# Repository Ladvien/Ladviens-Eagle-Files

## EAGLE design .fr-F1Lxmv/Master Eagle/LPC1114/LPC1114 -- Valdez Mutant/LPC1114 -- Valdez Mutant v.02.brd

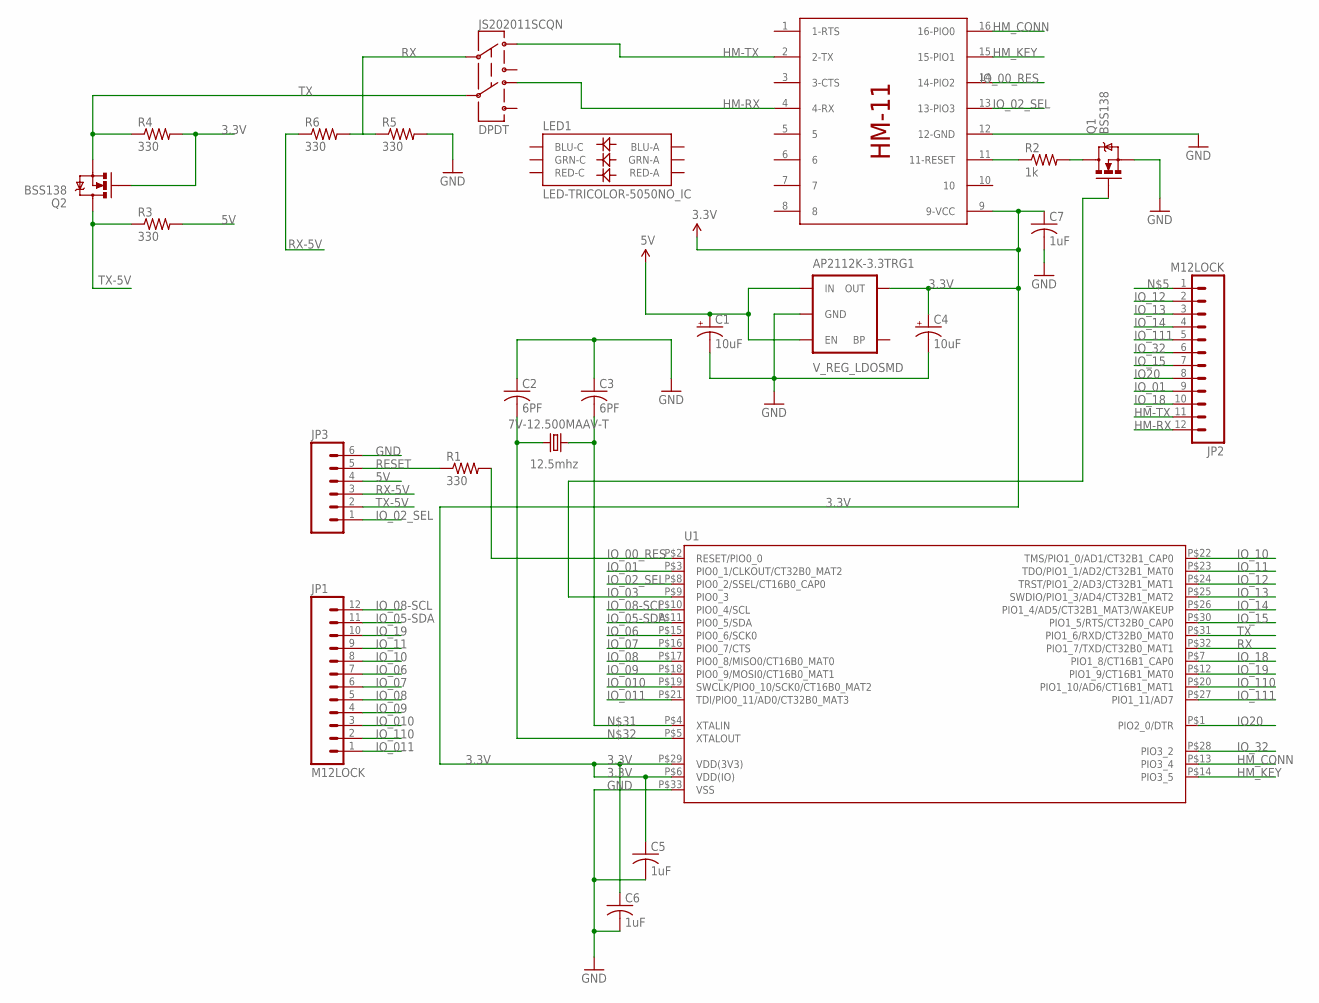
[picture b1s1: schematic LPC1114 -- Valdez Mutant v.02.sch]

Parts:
7V-12.500MAAV-T: 12.5mhz; CRYSTAL-SMD-5X3
AP2112K-3.3TRG1: V_REG_LDOSMD; SOT23-5
C1, C4: 10uF; EIA3216
C2, C3: 6PF; C0402K
C5, C6, C7: 1uF; C0402K
JP1, JP2: M12LOCK; 1X12_LOCK
JP3: M06LOCK; 1X06_LOCK
JS202011SCQN: DPDT; AYZ0202
LED1: LED-TRICOLOR-5050NO_IC; LED-TRICOLOR-5050
Q1, Q2: BSS138; SOT23
R1, R3, R4, R5, R6: 330; R0402
R2: 1k; R0402
U1: LPC1113/4_QFN; HVQFN33-7X7
U$1: HM-11

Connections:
3.3V: AP2112K-3.3TRG1.5 (OUT), C4.A (+), C5.1, C6.1, C7.1, Q2.1 (G), R4.2, U1.P$6 (VDD(IO)), U1.P$29 (VDD(3V3)), U$1.9 (9-VCC)
5V: AP2112K-3.3TRG1.1 (IN), AP2112K-3.3TRG1.3 (EN), C1.A (+), JP3.4, R3.2
GND: AP2112K-3.3TRG1.2 (GND), C1.C (-), C2.1, C3.1, C4.C (-), C5.2, C6.2, C7.2, JP3.6, Q1.2 (S), R5.2, U1.P$33 (VSS), U$1.12 (12-GND)
HM-RX: JP2.12, JS202011SCQN.4, U$1.4 (4-RX)
HM-TX: JP2.11, JS202011SCQN.1, U$1.2 (2-TX)
HM_CONN: U1.P$13 (PIO3_4), U$1.16 (16-PIO0)
HM_KEY: U1.P$14 (PIO3_5), U$1.15 (15-PIO1)
IO20: JP2.8, U1.P$1 (PIO2_0/DTR)
IO_00_RES: R1.2, U1.P$2 (RESET/PIO0_0), U$1.14 (14-PIO2)
IO_01: JP2.9, U1.P$3 (PIO0_1/CLKOUT/CT32B0_MAT2)
IO_02_SEL: JP3.1, U1.P$8 (PIO0_2/SSEL/CT16B0_CAP0), U$1.13 (13-PIO3)
IO_03: Q1.1 (G), U1.P$9 (PIO0_3)
IO_05-SDA: JP1.11, U1.P$11 (PIO0_5/SDA)
IO_06: JP1.7, U1.P$15 (PIO0_6/SCK0)
IO_07: JP1.6, U1.P$16 (PIO0_7/CTS)
IO_08: JP1.5, U1.P$17 (PIO0_8/MISO0/CT16B0_MAT0)
IO_08-SCL: JP1.12, U1.P$10 (PIO0_4/SCL)
IO_09: JP1.4, U1.P$18 (PIO0_9/MOSI0/CT16B0_MAT1)
IO_10: JP1.8, U1.P$22 (TMS/PIO1_0/AD1/CT32B1_CAP0)
IO_010: JP1.3, U1.P$19 (SWCLK/PIO0_10/SCK0/CT16B0_MAT2)
IO_11: JP1.9, U1.P$23 (TDO/PIO1_1/AD2/CT32B1_MAT0)
IO_011: JP1.1, U1.P$21 (TDI/PIO0_11/AD0/CT32B0_MAT3)
IO_12: JP2.2, U1.P$24 (TRST/PIO1_2/AD3/CT32B1_MAT1)
IO_13: JP2.3, U1.P$25 (SWDIO/PIO1_3/AD4/CT32B1_MAT2)
IO_14: JP2.4, U1.P$26 (PIO1_4/AD5/CT32B1_MAT3/WAKEUP)
IO_15: JP2.7, U1.P$30 (PIO1_5/RTS/CT32B0_CAP0)
IO_18: JP2.10, U1.P$7 (PIO1_8/CT16B1_CAP0)
IO_19: JP1.10, U1.P$12 (PIO1_9/CT16B1_MAT0)
IO_32: JP2.6, U1.P$28 (PIO3_2)
IO_110: JP1.2, U1.P$20 (PIO1_10/AD6/CT16B1_MAT1)
IO_111: JP2.5, U1.P$27 (PIO1_11/AD7)
unnamed: Q1.3 (D), R2.2
unnamed: R2.1, U$1.11 (11-RESET)
unnamed: 7V-12.500MAAV-T.3 (2), C3.2, U1.P$4 (XTALIN)
unnamed: 7V-12.500MAAV-T.1, C2.2, U1.P$5 (XTALOUT)
RESET: JP3.5, R1.1
RX: JS202011SCQN.2, R5.1, R6.2, U1.P$32 (PIO1_7/TXD/CT32B0_MAT1)
RX-5V: JP3.3, R6.1
TX: JS202011SCQN.5, Q2.2 (S), R4.1, U1.P$31 (PIO1_6/RXD/CT32B0_MAT0)
TX-5V: JP3.2, Q2.3 (D), R3.1

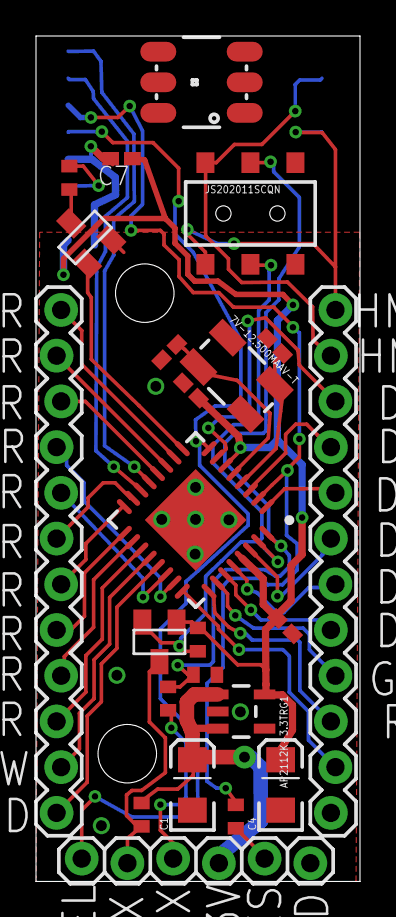
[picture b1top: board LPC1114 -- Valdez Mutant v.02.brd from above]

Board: 2 copper layers, 18.0 x 47.0 mm, 24 parts (1 on the bottom side), 40 nets.

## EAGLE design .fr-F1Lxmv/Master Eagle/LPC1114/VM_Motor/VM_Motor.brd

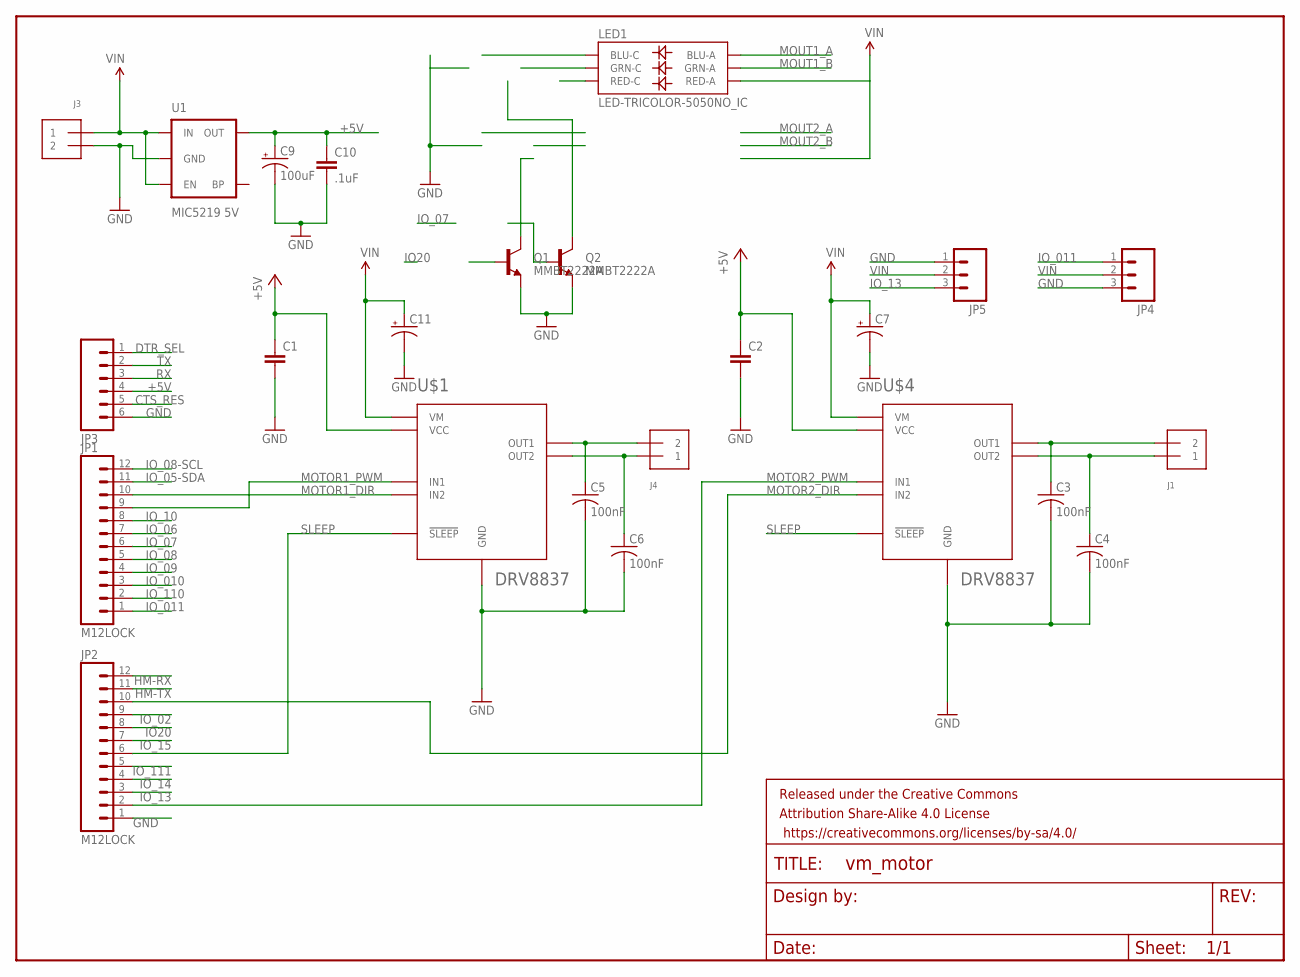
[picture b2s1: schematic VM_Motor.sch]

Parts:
C1, C2: CAP0402-CAP; 0402-CAP
C3, C4, C5, C6: 100nF; C0402
C7, C11: CPOL-US140CLH-0810; 140CLH-0810
C9: 100uF; EIA3528-KIT
C10: .1uF; 0402-CAP
FRAME1: FRAME-LETTER; CREATIVE_COMMONS
J1, J3, J4: TERMBLOCK_1X2; TERMBLOCK_1X2-3.5MM
JP1, JP2: M12LOCK; 1X12_LOCK
JP3: M06LOCK; 1X06_LOCK
JP4, JP5: M03LOCK; 1X03_LOCK
LED1: LED-TRICOLOR-5050NO_IC; LED-TRICOLOR-5050
Q1, Q2: MMBT2222A; SOT23-3
U1: MIC5219 5V; SOT23-5
U$1, U$4: DRV8837; QFN8

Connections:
+5V: C1.1, C2.1, C9.A (+), C10.1, JP3.4, U1.5 (OUT), U$1.P$8 (VCC), U$4.P$8 (VCC)
CTS_RES: JP3.5
DTR_SEL: JP3.1
GND: C1.2, C2.2, C3.2, C4.2, C5.2, C6.2, C7.-, C9.C (-), C10.2, C11.-, J3.2, JP2.1, JP3.6, JP4.3, JP5.1, Q1.2 (E), Q2.2 (E), U1.2 (GND), U$1.P$4 (GND), U$1.P$9 (GND), U$1.P$10 (GND), U$1.P$11 (GND), U$4.P$4 (GND), U$4.P$9 (GND), U$4.P$10 (GND), U$4.P$11 (GND)
HM-RX: JP2.12
HM-TX: JP2.11
IO20: JP2.8
IO_02: JP2.9
IO_05-SDA: JP1.11
IO_06: JP1.7
IO_07: JP1.6
IO_08: JP1.5
IO_08-SCL: JP1.12
IO_09: JP1.4
IO_10: JP1.8
IO_010: JP1.3
IO_011: JP1.1, JP4.1
IO_13: JP2.3, JP5.3
IO_14: JP2.4
IO_15: JP2.7
IO_110: JP1.2
IO_111: JP2.5
MOTOR1_DIR: JP1.10, U$1.P$5 (IN2)
MOTOR1_PWM: JP1.9, U$1.P$6 (IN1)
MOTOR2_DIR: JP2.10, U$4.P$5 (IN2)
MOTOR2_PWM: JP2.2, U$4.P$6 (IN1)
MOUT1_A: C5.1, J4.2, LED1.3 (BLU-A), U$1.P$2 (OUT1)
MOUT1_B: C6.1, J4.1, LED1.1 (GRN-A), U$1.P$3 (OUT2)
MOUT2_A: C3.1, J1.2, U$4.P$2 (OUT1)
MOUT2_B: C4.1, J1.1, U$4.P$3 (OUT2)
RX: JP3.3
SLEEP: JP2.6, U$1.P$7 (!SLEEP), U$4.P$7 (!SLEEP)
TX: JP3.2
VIN: C7.+, C11.+, J3.1, JP4.2, JP5.2, LED1.2 (RED-A), U1.1 (IN), U1.3 (EN), U$1.P$1 (VM), U$4.P$1 (VM)

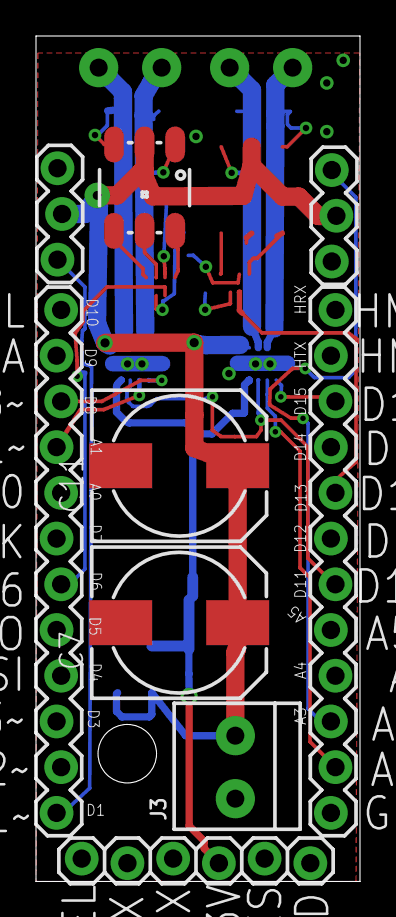
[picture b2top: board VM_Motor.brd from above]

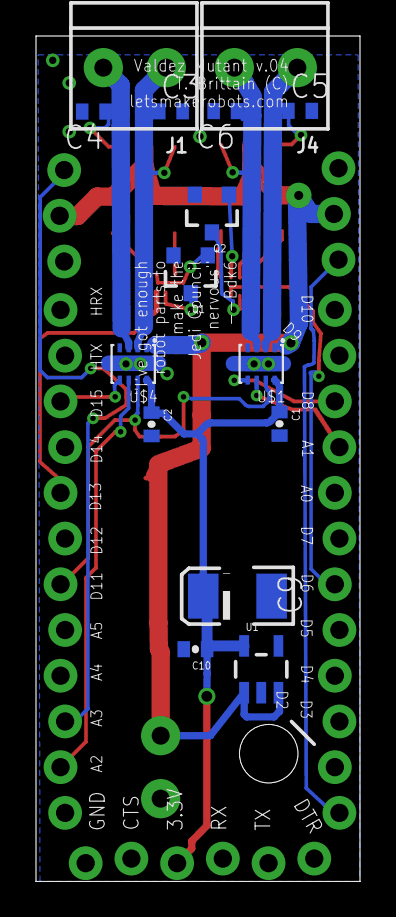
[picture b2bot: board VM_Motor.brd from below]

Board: 2 copper layers, 18.0 x 47.0 mm, 27 parts (16 on the bottom side), 14 nets.

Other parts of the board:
U$2, U$3: OSHW_FILLX100_NOTEXT

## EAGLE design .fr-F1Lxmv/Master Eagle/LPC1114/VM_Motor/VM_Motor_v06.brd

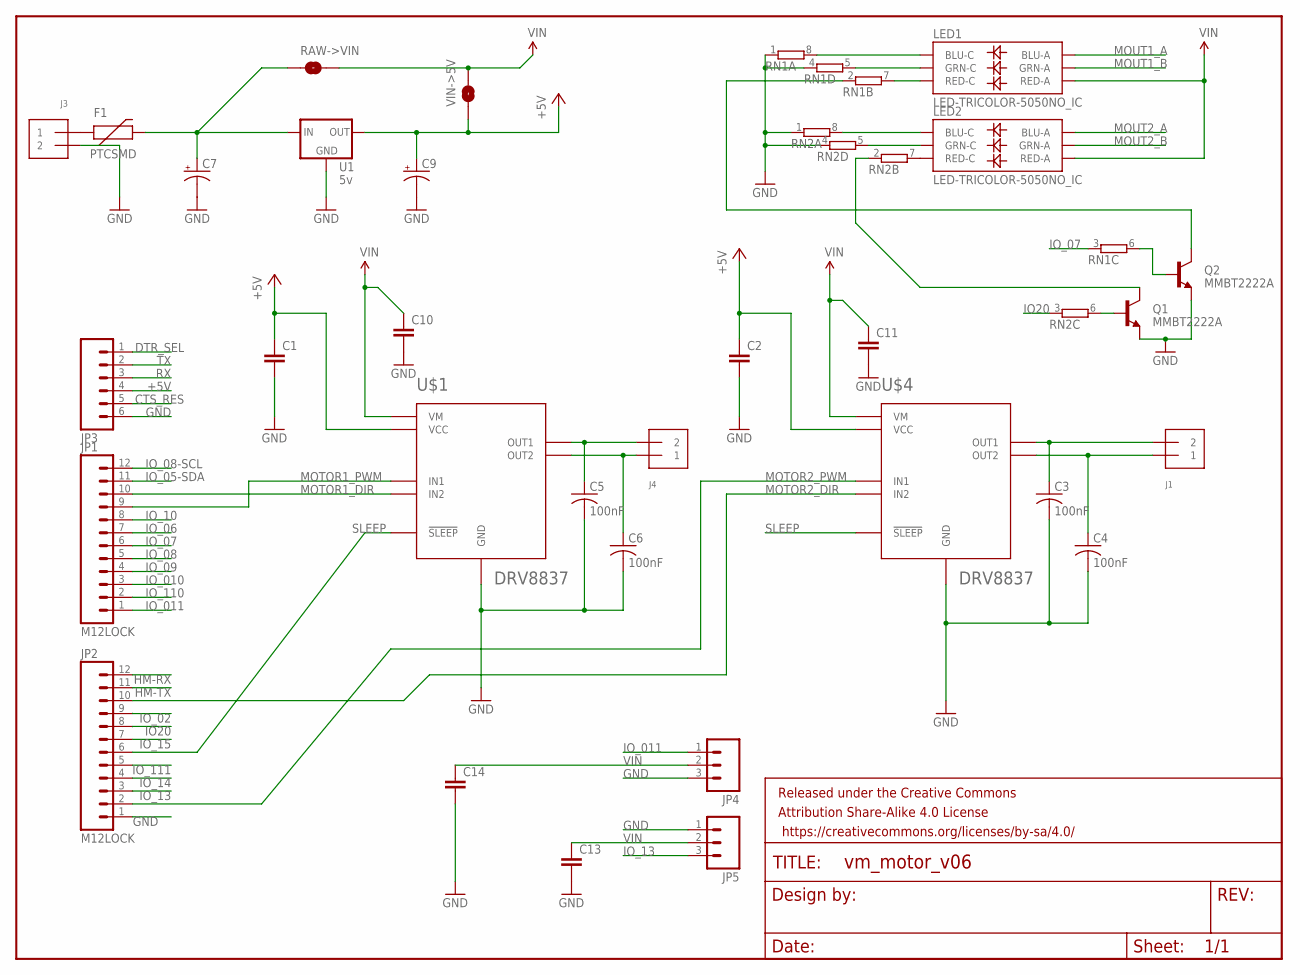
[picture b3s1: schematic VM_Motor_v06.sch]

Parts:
C1, C2, C10, C11, C13, C14: CAP0402-CAP; 0402-CAP
C3, C4, C5, C6: 100nF; C0402
C7, C9: CPOL-US150CLZ-0810; 150CLZ-0810
F1: PTCSMD; PTC-1206
FRAME1: FRAME-LETTER; CREATIVE_COMMONS
J1, J3, J4: TERMBLOCK_1X2; TERMBLOCK_1X2-3.5MM
JP1, JP2: M12LOCK; 1X12_LOCK
JP3: M06LOCK; 1X06_LOCK
JP4, JP5: M03LOCK; 1X03_LOCK
LED1, LED2: LED-TRICOLOR-5050NO_IC; LED-TRICOLOR-5050
Q1, Q2: MMBT2222A; SOT23-3
RAW->VIN: SOLDERJUMPERNO; SJ_2S-NO
RN1, RN2: 4R-N0402ARV341; 4X0402ARV341
U1: 5v; DPAK
U$1, U$4: DRV8837; QFN8
VIN->5V: SOLDERJUMPERNO; SJ_2S-NO

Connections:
+5V: C1.1, C2.1, C9.+, JP3.4, U1.4 (OUT), U$1.P$8 (VCC), U$4.P$8 (VCC), VIN->5V.1
CTS_RES: JP3.5
DTR_SEL: JP3.1
GND: C1.2, C2.2, C3.2, C4.2, C5.2, C6.2, C7.-, C9.-, C10.2, C11.2, C13.2, C14.2, J3.2, JP2.1, JP3.6, JP4.3, JP5.1, Q1.2 (E), Q2.2 (E), RN1.1, RN1.4 (1), RN2.1, RN2.4 (1), U1.1 (GND), U$1.P$4 (GND), U$1.P$9 (GND), U$1.P$10 (GND), U$1.P$11 (GND), U$4.P$4 (GND), U$4.P$9 (GND), U$4.P$10 (GND), U$4.P$11 (GND)
HM-RX: JP2.12
HM-TX: JP2.11
IO20: JP2.8, RN2.3 (1)
IO_02: JP2.9
IO_05-SDA: JP1.11
IO_06: JP1.7
IO_07: JP1.6, RN1.3 (1)
IO_08: JP1.5
IO_08-SCL: JP1.12
IO_09: JP1.4
IO_10: JP1.8
IO_010: JP1.3
IO_011: JP1.1, JP4.1
IO_13: JP2.3, JP5.3
IO_14: JP2.4
IO_15: JP2.7
IO_110: JP1.2
IO_111: JP2.5
MOTOR1_DIR: JP1.10, U$1.P$5 (IN2)
MOTOR1_PWM: JP1.9, U$1.P$6 (IN1)
MOTOR2_DIR: JP2.10, U$4.P$5 (IN2)
MOTOR2_PWM: JP2.2, U$4.P$6 (IN1)
MOUT1_A: C5.1, J4.2, LED1.3 (BLU-A), U$1.P$2 (OUT1)
MOUT1_B: C6.1, J4.1, LED1.1 (GRN-A), U$1.P$3 (OUT2)
MOUT2_A: C3.1, J1.2, LED2.3 (BLU-A), U$4.P$2 (OUT1)
MOUT2_B: C4.1, J1.1, LED2.1 (GRN-A), U$4.P$3 (OUT2)
unnamed: Q1.1 (B), RN2.6 (2)
unnamed: LED1.4 (BLU-C), RN1.8 (2)
unnamed: LED1.6 (GRN-C), RN1.5 (2)
unnamed: LED2.4 (BLU-C), RN2.8 (2)
unnamed: LED1.5 (RED-C), RN1.7 (2)
unnamed: Q1.3 (C), RN2.2 (1)
unnamed: Q2.3 (C), RN1.2 (1)
unnamed: Q2.1 (B), RN1.6 (2)
unnamed: LED2.6 (GRN-C), RN2.5 (2)
unnamed: LED2.5 (RED-C), RN2.7 (2)
unnamed: F1.1, J3.1
RAW: C7.+, F1.2, RAW->VIN.1, U1.3 (IN)
RX: JP3.3
SLEEP: JP2.6, U$1.P$7 (!SLEEP), U$4.P$7 (!SLEEP)
TX: JP3.2
VIN: C10.1, C11.1, C13.1, C14.1, JP4.2, JP5.2, LED1.2 (RED-A), LED2.2 (RED-A), RAW->VIN.2, U$1.P$1 (VM), U$4.P$1 (VM), VIN->5V.2

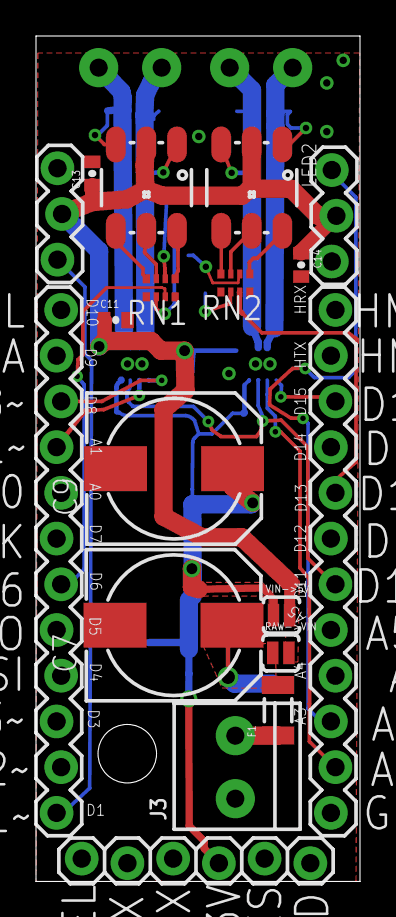
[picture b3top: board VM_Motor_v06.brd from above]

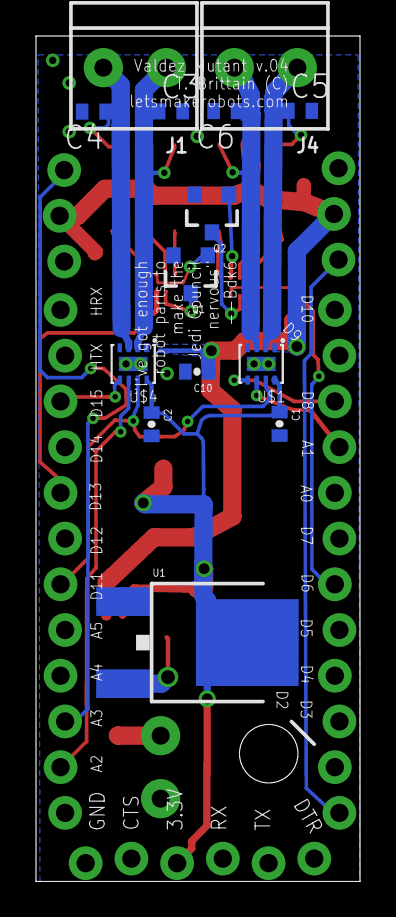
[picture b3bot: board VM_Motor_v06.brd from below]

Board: 2 copper layers, 18.0 x 47.0 mm, 35 parts (15 on the bottom side), 28 nets.

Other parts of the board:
U$2, U$3: OSHW_FILLX100_NOTEXT

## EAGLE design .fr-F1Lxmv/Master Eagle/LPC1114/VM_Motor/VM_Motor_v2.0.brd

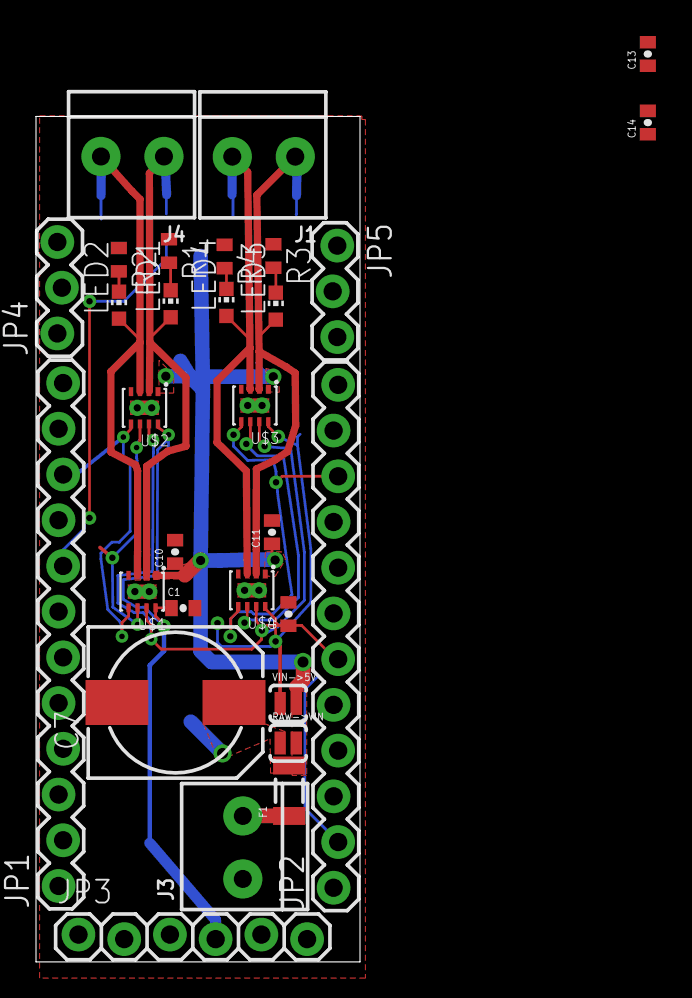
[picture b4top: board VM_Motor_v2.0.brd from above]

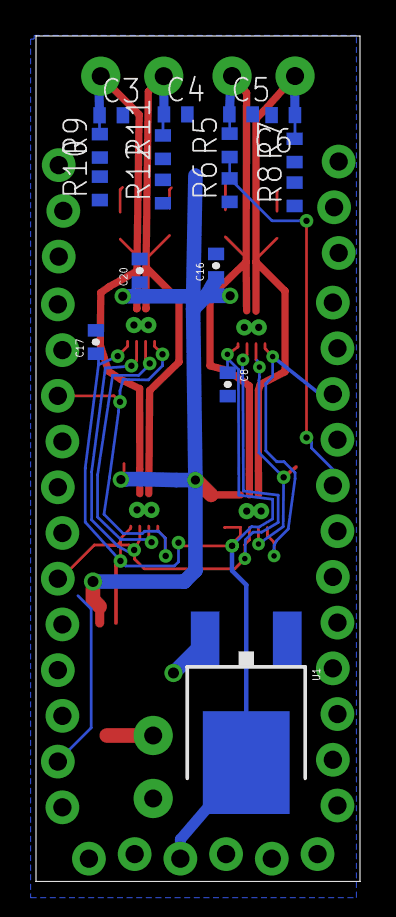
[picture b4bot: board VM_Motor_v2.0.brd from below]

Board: 2 copper layers, 18.0 x 47.0 mm, 47 parts (17 on the bottom side), 24 nets.

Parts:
C1, C2, C8, C17: .1uF; 0402-CAP
C3, C4, C5, C6: 100nF; C0402
C7: 1000uF; 150CLZ-0810
C10, C11, C13, C14, C16, C20: 10uF; 0402-CAP
F1: PTCSMD; PTC-1206
J1, J3, J4: TERMBLOCK_1X2-3.5MM
JP1, JP2: M12LOCK; 1X12_LOCK
JP3: 1X06_LOCK
JP4, JP5: 1X03_LOCK
LED1, LED3: BLUE; CHIP-LED0603
LED2, LED4: GREEN; CHIP-LED0603
R1, R2, R3, R4, R5, R6, R7, R8, R9, R10, R11, R12: R0402
RAW->VIN: SOLDERJUMPERNO; SJ_2S-NO
U1: V_REG_MC33269DT; DPAK
U$1, U$2, U$3, U$4: DRV8837; QFN8
VIN->5V: SOLDERJUMPERNO; SJ_2S-NO

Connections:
+5V: C1.1, C2.1, C8.1, C17.1, JP3.4, U1.4, U$1.P$8, U$2.P$8, U$3.P$8, U$4.P$8, VIN->5V.1
GND: C1.2, C2.2, C3.2, C4.2, C5.2, C6.2, C7.-, C8.2, C10.2, C11.2, C13.2, C14.2, C16.2, C17.2, C20.2, J3.2, JP2.1, JP3.6, JP4.3, JP5.1, R1.1, R2.1, R3.1, R4.1, R6.1, R8.1, R10.1, R12.1, U1.1, U$1.P$4, U$1.P$9, U$1.P$10, U$1.P$11, U$2.P$4, U$2.P$9, U$2.P$10, U$2.P$11, U$3.P$4, U$3.P$9, U$3.P$10, U$3.P$11, U$4.P$4, U$4.P$9, U$4.P$10, U$4.P$11
IO_10: JP1.8, R5.1, R6.2
IO_011: JP1.1, JP4.1
IO_11: JP1.9, R11.1, R12.2
IO_13: JP2.3, JP5.3
IO_110: JP1.2, R7.1, R8.2
IO_111: JP2.5, R9.1, R10.2
MOTOR1_DIR: JP1.10, U$1.P$5, U$2.P$5
MOTOR1_PWM: JP1.3, U$1.P$6, U$2.P$6
MOTOR2_DIR: JP2.10, U$3.P$5, U$4.P$5
MOTOR2_PWM: JP2.2, U$3.P$6, U$4.P$6
MOUT1_A: C5.1, J4.2, LED1.A, R5.2, U$1.P$2, U$2.P$2
MOUT1_B: C6.1, J4.1, LED2.A, R7.2, U$1.P$3, U$2.P$3
MOUT2_A: C3.1, J1.2, LED3.A, R9.2, U$3.P$2, U$4.P$2
MOUT2_B: C4.1, J1.1, LED4.A, R11.2, U$3.P$3, U$4.P$3
unnamed: LED2.C, R2.2
unnamed: LED4.C, R4.2
unnamed: LED1.C, R1.2
unnamed: LED3.C, R3.2
unnamed: F1.1, J3.1
RAW: C7.+, F1.2, RAW->VIN.1, U1.3
SLEEP: JP2.6, U$1.P$7, U$2.P$7, U$3.P$7, U$4.P$7
VIN: C10.1, C11.1, C13.1, C14.1, C16.1, C20.1, JP4.2, JP5.2, RAW->VIN.2, U$1.P$1, U$2.P$1, U$3.P$1, U$4.P$1, VIN->5V.2

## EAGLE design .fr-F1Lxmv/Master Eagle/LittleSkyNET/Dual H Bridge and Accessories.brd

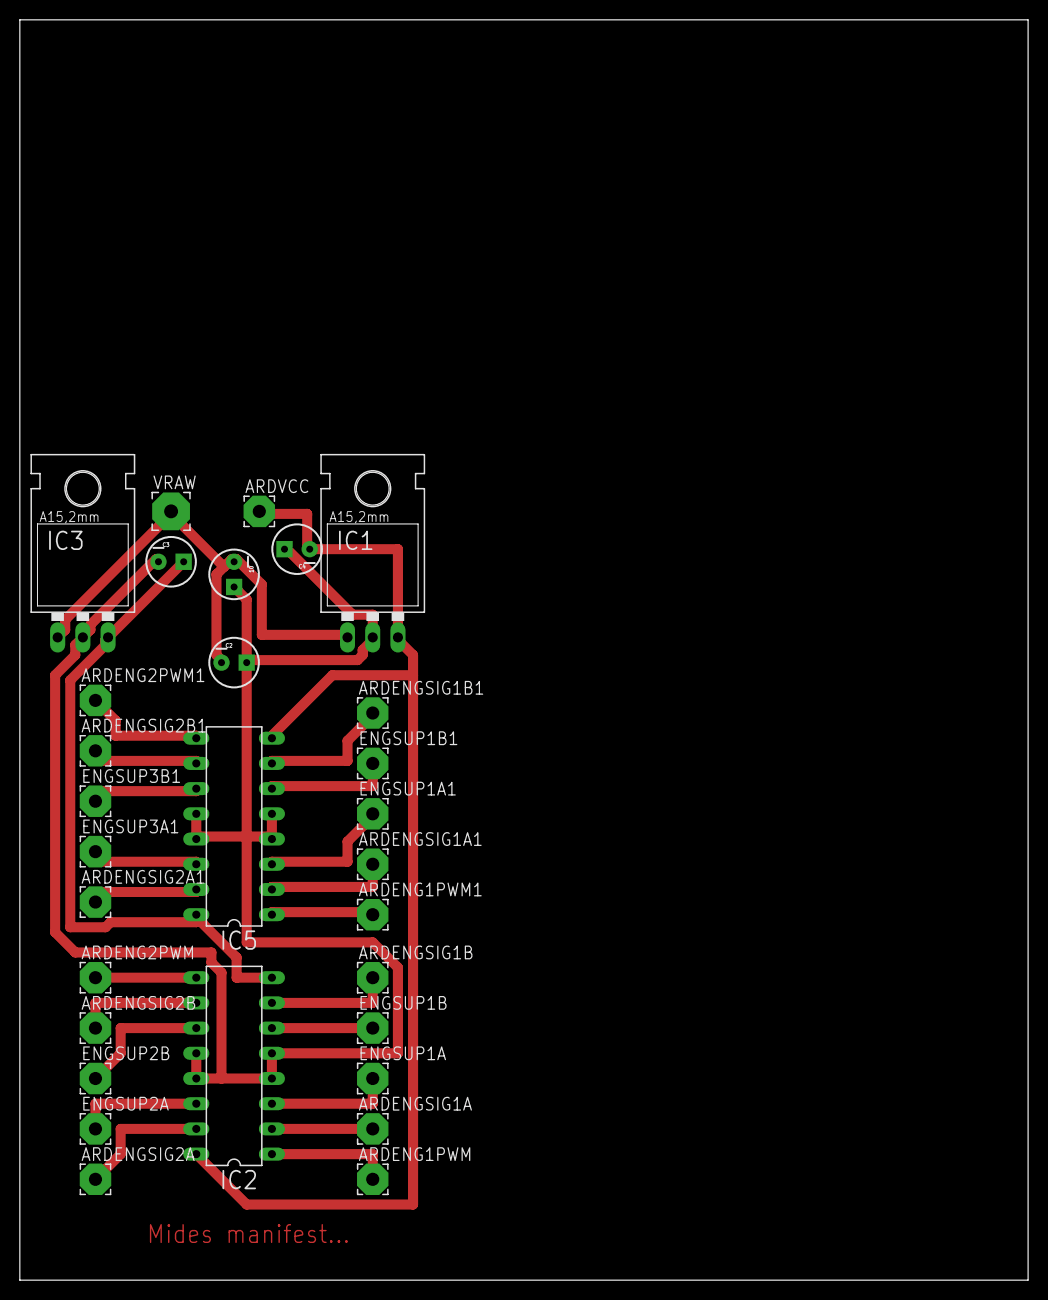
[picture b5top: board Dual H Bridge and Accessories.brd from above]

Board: 2 copper layers, 101.6 x 127.0 mm, 30 parts (0 on the bottom side), 24 nets.

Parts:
10: 10; CPOL-RADIAL-10UF-25V
ARDENG1PWM, ARDENG1PWM1: Eng 1 Pwm; 3,17/1,3
ARDENG2PWM, ARDENG2PWM1: Eng2 Pwm; 3,17/1,3
ARDENGSIG1A, ARDENGSIG1A1: Eng Sig 1A; 3,17/1,3
ARDENGSIG1B, ARDENGSIG1B1: Eng Sig 1B; 3,17/1,3
ARDENGSIG2A, ARDENGSIG2A1: Eng Sig 2A; 3,17/1,3
ARDENGSIG2B, ARDENGSIG2B1: Eng Sig 2B; 3,17/1,3
ARDVCC: Ard VCC; 3,17/1,3
C2: 10; CPOL-RADIAL-10UF-25V
C3, C4: .1; CPOL-RADIAL-10UF-25V
ENGSUP1A, ENGSUP1A1: Eng Sup 1A; 3,17/1,3
ENGSUP1B, ENGSUP1B1: Eng Sup 1B; 3,17/1,3
ENGSUP2A, ENGSUP3A1: Eng Sup 2A; 3,17/1,3
ENGSUP2B, ENGSUP3B1: Eng Sup 2B; 3,17/1,3
IC1: 5v; 78XXL
IC2, IC5: SN754410; DIP16
IC3: 12v; 78XXL
VRAW: VRaw; 3,81/1,4

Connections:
ARDENGSIG1A: ARDENGSIG1A.1, IC2.2
ARDENGSIG1A1: ARDENGSIG1A1.1, IC5.2
ARDENGSIG1B: ARDENGSIG1B.1, IC2.7
ARDENGSIG1B1: ARDENGSIG1B1.1, IC5.7
ARDENGSIG2B: ARDENGSIG2B.1, IC2.10
ARDENGSIG2B1: ARDENGSIG2B1.1, IC5.10
GND: 10.1, C2.1, C3.2, C4.1, IC1.GND, IC2.4, IC2.5, IC2.12, IC2.13, IC3.GND, IC5.4, IC5.5, IC5.12, IC5.13
unnamed: 10.2, C2.2, IC1.IN, IC3.IN, VRAW.1
unnamed: ARDENG1PWM.1, IC2.1
unnamed: ARDENG2PWM.1, IC2.9
unnamed: ARDENGSIG2A.1, IC2.15
unnamed: ARDENG1PWM1.1, IC5.1
unnamed: ENGSUP1A.1, IC2.3
unnamed: ENGSUP1B.1, IC2.6
unnamed: ENGSUP2B.1, IC2.11
unnamed: ENGSUP2A.1, IC2.14
unnamed: C3.1, IC2.8, IC3.OUT, IC5.16
unnamed: ARDENG2PWM1.1, IC5.9
unnamed: ARDENGSIG2A1.1, IC5.15
unnamed: ENGSUP1A1.1, IC5.3
unnamed: ENGSUP1B1.1, IC5.6
unnamed: ENGSUP3B1.1, IC5.11
unnamed: ENGSUP3A1.1, IC5.14
unnamed: ARDVCC.1, C4.2, IC1.OUT, IC2.16, IC5.8

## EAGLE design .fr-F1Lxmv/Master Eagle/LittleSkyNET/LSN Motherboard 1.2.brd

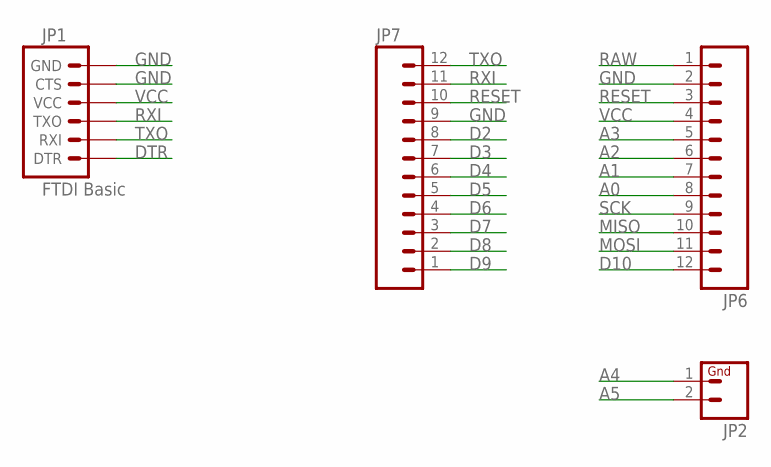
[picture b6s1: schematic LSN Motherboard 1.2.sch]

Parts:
JP1: FTDI Basic; 1X06
JP2: M02PTH; 1X02
JP6, JP7: M12PTH; 1X12

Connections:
A0: JP6.8
A1: JP6.7
A2: JP6.6
A3: JP6.5
A4: JP2.1
A5: JP2.2
D2: JP7.8
D3: JP7.7
D4: JP7.6
D5: JP7.5
D6: JP7.4
D7: JP7.3
D8: JP7.2
D9: JP7.1
D10: JP6.12
DTR: JP1.1 (DTR)
GND: JP1.5 (CTS), JP1.6 (GND), JP6.2, JP7.9
MISO: JP6.10
MOSI: JP6.11
RAW: JP6.1
RESET: JP6.3, JP7.10
RXI: JP1.3 (TXO), JP7.11
SCK: JP6.9
TXO: JP1.2 (RXI), JP7.12
VCC: JP1.4 (VCC), JP6.4

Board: 2 copper layers, 4 parts (4 on the bottom side), 5 nets, no tracks yet.

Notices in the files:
parts and their libraries:
microbuilder: This work is placed in the public domain, and may be freely used for commercial and non-commercial work with the following conditions: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
SparkFun-Connectors: Licensing: Creative Commons ShareAlike 4.0 International - https://creativecommons.org/licenses/by-sa/4.0
